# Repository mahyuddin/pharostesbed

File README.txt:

This is the software used by the Proteus robots in the Pharos
Mobile Computing Laboratory at UT.  The software is modularized into the
following directories:
   
 - PharosMiddleware: This is the middleware that runs on top of Player and
   provides higher-level operations.  For example, it helps coordinate
   the start of a multi-robot GPS-based navigation experiment, and performs
   GPS-based waypoint navigation.  This is written in Java.

 - Proteus2: Contains the software used by the Proteus 2 robot.

 - Proteus3: Contains the software used by the Proteus 3 robot.

 - Scripts: This contains scripts that are useful for parsing the log
   files generated by the Pharos Middleware.

 - Utils: Contains small programs that are useful for running multi-robot 
   experiments.

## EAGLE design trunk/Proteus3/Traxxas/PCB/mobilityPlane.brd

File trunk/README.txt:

This is the software used by the Proteus robots in the Pharos
Mobile Computing Laboratory at UT.  The software is modularized into the
following directories:

 - MCU: This is the code that runs on the 9S12 micro-controller. This is 
   written in C.
 
 - MCU-SimonSays: This is the 9S12 MCU code for the Simon Says demo.

 - ProteusDriver: This is the Player Driver that allows the Player
   middleware to communicate with the robot's MCU.  The Player middleware
   provides basic access to robot sensors and actuators, e.g., movement
   and sensing commands.  This is written in C/C++.

 - Mote: This is the software that runs on the TelosB mote, which contains
   a MSP430 MCU and 802.15.4 wireless interface.  It is written in NesC,
   and requires the TinyOS operating system.
   
 - PharosMiddleware: This is the middleware that runs on top of Player and
   provides higher-level operations.  For example, it helps coordinate
   the start of a multi-robot GPS-based navigation experiment, and performs
   GPS-based waypoint navigation.  This is written in Java.

 - Proteus3: Contains the software used by the Proteus 3 robot.

 - Scripts: This contains scripts that are useful for parsing the log
   files generated by the Pharos Middleware.

 - Utils: Contains small programs that are useful for running multi-robot 
   experiments.

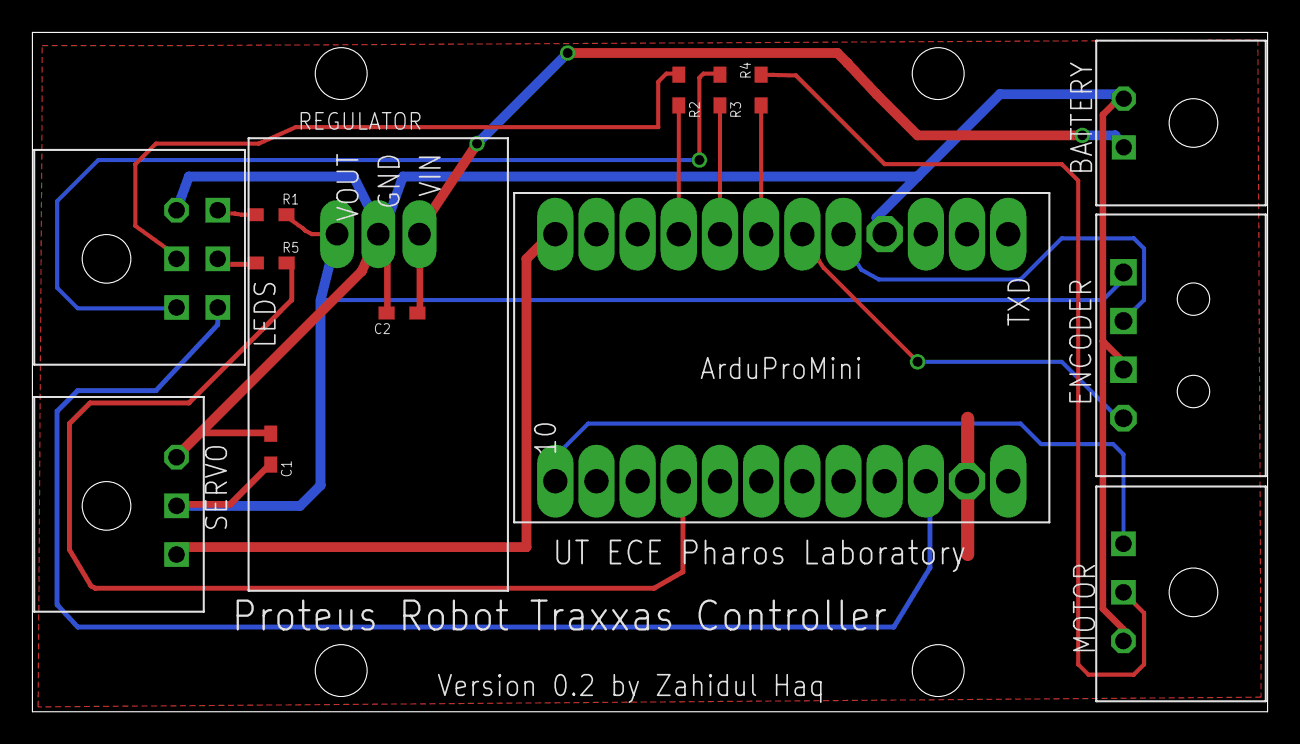
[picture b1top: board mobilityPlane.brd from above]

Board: 2 copper layers, 76.2 x 41.9 mm, 14 parts (0 on the bottom side), 11 nets.

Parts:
ARDUINOMINIPRO: ARDUMINI
BATTERY: BATTERY; LED
C1, C2: SMDRESISTOR
ENCODER: ENCODER; LOCK4PIN
LEDS: LED4PIN; LOCK6PIN
MOTOR: SERIAL; LOCK3PIN
R1, R2, R3, R4, R5: SMDRESISTOR
REGULATOR: REGULATOR
SERVO: SERVO; LOCK3PIN

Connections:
GND: ARDUINOMINIPRO.GND, BATTERY.-, ENCODER.P$2, LEDS.(-), MOTOR.(-), REGULATOR.GND, SERVO.(-)
unnamed: ARDUINOMINIPRO.9, SERVO.P$3
unnamed: ARDUINOMINIPRO.10, MOTOR.P$3
unnamed: ARDUINOMINIPRO.2, ENCODER.P$3
unnamed: ARDUINOMINIPRO.3, ENCODER.(-)
unnamed: ENCODER.P$4, REGULATOR.VOUT, SERVO.P$2
unnamed: ARDUINOMINIPRO.5, R3.(+)
unnamed: MOTOR.P$2, R4.(+)
unnamed: ARDUINOMINIPRO.6, R2.(+)
unnamed: ARDUINOMINIPRO.4, R4.(-)
PWR: BATTERY.+, REGULATOR.VIN

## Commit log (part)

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2012-01-10 Removed unused variable.
2012-01-10 Start the line follower after the player client is set to run in threaded mode.
2012-01-10 Initial commit.
2012-01-10 Updated javadoc.
2012-01-10 Removed unused packages.
2012-01-10 Removed unused variables.
2012-01-10 This is compatible with 64-bit OSX.
2012-01-10 Removed unnecessary program.
2012-01-10 Added javadoc.
2012-01-10 Updated command line arguments.
2012-01-10 Added option to control whether debug mode is initially enabled.
2012-01-10 Updated javadoc. Modified sendMessage to return a boolean indicating whether message transmission was successful.
2012-01-10 Modified the sendMessage method to be synchronous and return a boolean value indicating whether it was successful.
2012-01-10 Removed since it is replaced with AckedMsg.
2012-01-10 Simplified the messaging scheme in the simon says demo (it now uses the AckedMsg interface provided by the Pharos Middleware). Modified the SimonSays server to disconnect from player after each comma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
2012-01-11 Removed MCU-AutoInt
2012-01-11 This is a branch for the Simon Says project.
2012-01-13 Added infrastructure to allow Scratch to communicate with PharosMiddleware and created 2 tests of the interface.
2012-01-13 ScratchIO can now handle receiving multiple sensor updates in the same message.
2012-01-13 Commented out output statements and fixed indentation.
2012-01-13 Initial implementation of Scratch-Robot implementation.
2012-01-20 Added all message types to SimonSaysScratch but still need to implement camera controls. Added ability to make CreateRobotInterface when not on the actual robot.
2012-01-24 Initial implementation of passing variables from Java to Scratch. Will probably need to split it out into its own thread.
2012-01-25 initial commit of CPSAssertionFramework for FSE 2012. This codebase is 100% separate from the SimonSaysDemo. Currently supports CP property mapping and sending general messages between Client and Ser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
2012-01-26 mapping of logical references to cyber-physical properties is working and tested.
2012-02-03 Implemented a new Linefollower2 algorithm.
2012-02-08 Added Proteus3 directory in repository
2012-02-08 Added readme and SteeringAngleSweep
2012-02-08 Added Encoder Test program
2012-02-08 Added SpeedSteeringManualControl
2012-02-08 Added safety shutoff (untested). Renamed file using new extension.
2012-02-09 Added Driver_v1
2012-02-09 Changed MOTOR_STOP value from 85 to 84
2012-02-09 Fixed bug that set target speed to non-zero value during safety stop
2012-02-09 Added a simple driver (v1). Tested to work, though sometimes the response messages are off-sync resulting in data corruption.
2012-02-09 Added description of Driver_v1
2012-02-09 Debugged. Tested to work
2012-02-09 Added start byte and checksum to response message.
2012-02-09 Fixed bug in calculation of steering angle command. Added additional test cases for stering and driving in reverse.
2012-02-09 Shorted safety stop interval to 0.5s
2012-02-11 Fixed grammar
2012-02-11 Added README.txt
2012-02-14 removed extraneous directory.
2012-02-14 modified to allow user to decide when to send the start byte to the motor controller
2012-02-15 Added tests.
2012-02-15 Changed baud rate to be 19200
2012-02-23 Reorganized directory structure to include Proteus 3 software
2012-02-23 Moved Mote into Proteus2 compute plane directory and added README.txt to that directory.
2012-02-23 Set svn ignore on directories containing binary data
2012-02-23 Merged latest changes from trunk into this branch
2012-02-23 Added MCU code for interfacing with 9S12 microcontroller from last Fall 2011
2012-02-24 Fixed misspelling in Javadoc.
2012-02-25 Added ExpCoordinator, MRPatrol2Server, and skeletal code for uncoordinated outdoor experiments.
2012-02-25 Added the outdoor patrol daemon.
2012-02-25 Implemented UncoordinatedPatrolDaemon though it is still untested.
2012-02-26 Implemented simple behavior programming model. Tested the ExpConfig class' ability to read in a configuration file.
2012-02-26 Moved WiFi beacons from MRPatrol2Server into PatrolDaemon. Cleaned up the code a little. Created thread for PatrolDaemon.
2012-02-26 Added check for invalid coordination type.
2012-02-26 Added an initial (incomplete) implementation of the world model.
2012-02-26 Added timestamps to beacons so we can judge time synchronization among the teammates.
2012-02-26 Changed made during MM20. The uncoordinated patrol was tested to work.
2012-02-27 Moved world model into context package.
2012-02-27 Updated usage instructions.
2012-02-27 Changed compass index from 1 to 2 to be compatible with arduino-based compass.
2012-02-29 Fixed bug that prevented date from being set on the robots. Added a tool called SetTimeCoordinator for setting the system clocks on all of the robots. Modified BehaviorWaitTime to always set the refe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
2012-02-29 Added support for passive coordination. This is when the robots only coordinate after arriving at a waypoint. Currently, beacons only contain the information of the transmitter.
2012-03-01 Bug fixes made during M38.
2012-03-01 Added anticipated fixed patrol.
2012-03-02 Added dynamic anticipated coordination, though it doesn't compile yet.
2012-03-06 Modified to implement the Message interface so that it can be transmitted using TCP. Removed the anticipated local variable.
2012-03-06 Modified to use the shared pharoslabut.util.Random class.
2012-03-06 Added method that retrieves teammate settings by name.
2012-03-06 Added TCP-based coordination.
2012-03-06 Modified TCP beacons to spawn a new thread for each transmission.
2012-03-06 Added temp code to make it compile OK.
2012-03-08 Bug fixes made during M39.
2012-03-10 Modified to use LineFollower2.
2012-03-12 Fixed misspelling in comments.
2012-03-13 Code for evasion planning in autonomous intersection project.
2012-03-13 Added readme
2012-03-20 Initial commit of visualizers for MRP2 experiments.
2012-03-20 Modified to only print the refresh cycle state if at least one behavior can be started.
2012-03-21 Modified to accept compass device index as command line parameter.
2012-03-21 Increased its polling frequency for new compass data.
2012-03-21 Modified to use events for receiving compass measurements, and only using the most recent compass measurement.
2012-03-21 Modified to use new Navigator API.
2012-03-21 Remove unused import.
2012-03-23 Implemented a new NavigateCompassGPS algorithm that works with the Traxxas 2.5 robot.
2012-03-23 Cleaned up the code a little.
2012-03-28 Changes made during Mission 40.
2012-03-28 Changed number of retries to zero.
2012-04-02 Fixed a bug that resulted in this behavior continuing to run despite its dependencies not being met.
2012-04-02 Removed import of unused packages.
2012-04-02 Shifted debug comments into debug log.
2012-04-02 Updated legend
2012-04-04 Changes made during M43.
2012-04-05 Modified to calculate wait times and multiple experiments.
2012-04-05 Fixed bug in computation of min/max values.
2012-04-05 Fixed a bug that caused one experiment to interfere with another experiment.
2012-04-05 Renamed to better describe what it does.
2012-04-05 Calibrated the patrol start time, updated method that returns the robot's name.
2012-04-05 Renamed this class.
2012-04-09 Added debug output.
2012-04-11 Fixed a bug that resulted in the last wait times of the starting nodes not being considered.
2012-04-11 Improved the formatting of the detailed tables.
2012-04-30 Changes made during M45.
2012-05-17 Added option to control which waypoint to initially head towards.
2012-05-25 Added time zone and offset on May 25, 2012.
2012-06-07 Added additional date offsets.
2012-06-07 Merged MRP2 branch
2012-06-07 Creating an MRP2 Simulation Branch
2012-06-15 Added directory for Pharos Visualizer
2012-06-18 Initial commit of ping test analyzer.
2012-07-03 Updated README.txt
2012-07-05 Tweaked code to remove compiler warnings.
2012-07-21 Changes made during Mission 50.
2012-07-23 Parameterized the comparable interface.
2012-07-30 Added bin directory
2012-07-30 modified to only compile the code when running ant
2012-08-01 Added comment
2012-08-17 Added debug statement.
2012-08-17 Modified to be compatible with the output of the Proteus III robot.
2012-08-31 Modified waypoints to be closer to the static node locations. Changed waypoint names to be north/south instead of src/sink since end points are now both sources and sinks.
2012-09-03 Changes made during M54.
2012-09-11 Rename original grapevine branch
2012-09-11 Create directory to hold egrim's branches
2012-09-11 Move grapevine branch into egrim's branches
2012-09-11 Move MRP into egrim's branches
2012-09-11 Clear out defunct branch (moved to egrim's branch dir)
2012-09-11 Create branch robotperimeter
2012-09-11 Add .gitignore file based on SVN ignores
2012-09-11 Add 'PharosMiddleware/src/pharoslabut/robotperimeter/' from commit '8b0e67c59238ab6e0beb3b52e089b9a60ef1748a'
    git-subtree-dir: PharosMiddleware/src/pharoslabut/robotperimeter
    git-subtree-mainline: 5a50b45470c2962af0a0d2f2bd66e24374d8d40a
    git-subtree-split: 8b0e67c59238ab6e0beb3b52e089b9a60ef1748a
2012-09-11 Add Nikhil's middleware mods
2012-09-11 Change package/classpath as needed for middleware integration
2012-09-11 Add Jama jar
2012-09-11 Fix reference in ContextHandler
2012-09-11 Clean-up imports
2012-09-11 Added missing generic parameter definitions
2012-09-11 Remove vestigial code
2012-09-12 Add additional logging to Vision class
2012-09-12 Begin transition to ExpServer style class
2012-09-19 Updated to new file extension. Increased sweep speed.
